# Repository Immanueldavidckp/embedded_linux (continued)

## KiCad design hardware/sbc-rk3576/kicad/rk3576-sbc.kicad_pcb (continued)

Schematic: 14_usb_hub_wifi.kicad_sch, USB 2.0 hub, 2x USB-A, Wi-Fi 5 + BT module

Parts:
C1401: 4.7uF; C_0402_1005Metric; MPN 0402 4.7uF 10V X5R
C1402, C1412: 100nF; C_0402_1005Metric; MPN 0402 100nF 10V X5R
C1403: 10uF; C_0603_1608Metric; MPN 0603 10uF 10V X5R
C1404, C1405, C1407, C1415: 100nF; C_0402_1005Metric; MPN 0402 100nF 6.3V X5R
C1406, C1408, C1414: 1uF; C_0402_1005Metric; MPN 0402 1uF 6.3V X5R
C1409, C1410: 22pF; C_0402_1005Metric; MPN 0402 22pF 50V C0G
C1411: 47uF; C_0805_2012Metric; MPN 0805 47uF 10V X5R
C1413: 22uF; C_0603_1608Metric; MPN 0603 22uF 10V X5R
C1416, C1417: DNP; C_0402_1005Metric; MPN 0402 DNP 6.3V X5R; not fitted
FB1401, FB1402: 120R@100MHz; L_0603_1608Metric; MPN BLM18PG121SN1D
J1401: USB2.0 A x2; USB_A_CUI_UJ2-ADH-TH_Horizontal_Stacked; MPN UJ2-ADH-TH
J1402: u.FL; U.FL_Hirose_U.FL-R-SMT-1_Vertical; MPN U.FL-R-SMT-1(10)
Q1401: BSS138; SOT-23; MPN BSS138; LCSC C52895
R1401: 2.7k; R_0402_1005Metric; MPN 0402 2.7k 1%
R1402, R1403, R1404, R1405, R1406: 10k; R_0402_1005Metric; MPN 0402 10k 1%
R1407: 100k; R_0402_1005Metric; MPN 0402 100k 1%
R1408: 0R; R_0402_1005Metric; MPN 0402 0R 1%
U1401: FE1.1s; SSOP-28_3.9x9.9mm_P0.635mm; MPN FE1.1S-BSOP28BCN; LCSC C9359
U1402, U1403: USBLC6-2SC6; SOT-23-6; MPN USBLC6-2SC6; LCSC C7519
U1404: AP2171W; SOT-23-5; MPN AP2171WG-7; LCSC C155555
U1405: BL-M8821CU1; WiFi_Module_22P_13.0x12.2mm_P1.27mm; MPN BL-M8821CU1 (alt BL-M8723DU1, JLC C9900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
Y1401: 12MHz; Crystal_SMD_3225-4Pin_3.2x2.5mm; MPN X322512MSB4SI (12MHz 20pF); LCSC C9002

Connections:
GND: C1401.2, C1402.2, C1403.2, C1404.2, C1405.2, C1406.2, C1407.2, C1408.2, C1409.2, C1410.2, C1411.2, C1412.2, C1413.2, C1414.2, C1415.2, C1416.2, C1417.2, J1401.4 (GND1), J1401.8 (GND2), J1401.9 (Shield), J1402.2 (Ext), Q1401.2 (S), R1401.2, R1407.2, U1401.1 (VSS), U1402.2 (GND), U1403.2 (GND), U1404.2 (GND), U1405.1 (GND), U1405.4 (GND), U1405.14 (GND), Y1401.2 (G), Y1401.4 (G); also elsewhere on the board
HUB_1V8: C1406.1, C1407.1, U1401.12 (VD18_O), U1401.28 (VD18)
HUB_3V3: C1403.1, C1404.1, C1405.1, R1402.2, R1403.2, U1401.13 (VD33), U1401.18 (VBUSM), U1401.19 (BUSJ), U1401.21 (VD33_O)
HUB_OVC_L: R1403.1, U1401.26 (OVCJ), U1404.3 (~FLG)
HUB_REXT: R1401.1, U1401.14 (REXT)
HUB_RST_L: C1408.1, R1402.1, U1401.17 (XRSTJ)
HUB_UP_DM: U1401.15 (DMU); also elsewhere on the board
HUB_UP_DP: U1401.16 (DPU); also elsewhere on the board
HUB_XI: C1409.1, U1401.3 (XIN), Y1401.1
HUB_XO: C1410.1, U1401.2 (XOUT), Y1401.3
USB3A_DM: U1401.10 (DM1); also elsewhere on the board
USB3A_DP: U1401.11 (DP1); also elsewhere on the board
USBA1_DM: J1401.2 (D1-), U1401.8 (DM2), U1402.3 (I/O2), U1402.4 (I/O2)
USBA1_DP: J1401.3 (D1+), U1401.9 (DP2), U1402.1 (I/O1), U1402.6 (I/O1)
USBA2_DM: J1401.6 (D2-), U1401.6 (DM3), U1403.3 (I/O2), U1403.4 (I/O2)
USBA2_DP: J1401.7 (D2+), U1401.7 (DP3), U1403.1 (I/O1), U1403.6 (I/O1)
USB_HOST_PWREN: U1404.4 (EN); also elsewhere on the board
VBUS_USB2A: C1411.1, C1412.1, J1401.1 (VBUS1), J1401.5 (VBUS2), U1402.5 (VBUS), U1403.5 (VBUS), U1404.1 (OUT)
VCC3V3_WIFI: C1413.1, C1414.1, C1415.1, FB1402.2, R1404.2, R1405.2, R1406.2, U1405.11 (VDD33)
VCC5V0_SYS_S5: FB1401.1, U1404.5 (IN); also elsewhere on the board
VCC5V_HUB: C1401.1, C1402.1, FB1401.2, U1401.20 (VDD5)
VCC_3V3_S3: FB1402.1; also elsewhere on the board
WIFI_ANT: C1417.1, J1402.1 (In), R1408.2
WIFI_BT_DIS_L: R1405.1, U1405.17 (~BT_DIS)
WIFI_CHIP_EN: Q1401.3 (D), R1406.1, U1405.18 (CHIP_EN)
WIFI_PD_GPIO: Q1401.1 (G), R1407.1; also elsewhere on the board
WIFI_RF: C1416.1, R1408.1, U1405.2 (RF)
WIFI_USB_DM: U1401.4 (DM4), U1405.12 (USB_DM)
WIFI_USB_DP: U1401.5 (DP4), U1405.13 (USB_DP)
WIFI_WL_DIS_L: R1404.1, U1405.16 (~WL_DIS)

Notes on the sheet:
14_usb_hub_wifi: USB 2.0 hub, 2x USB-A, Wi-Fi 5 + BT module

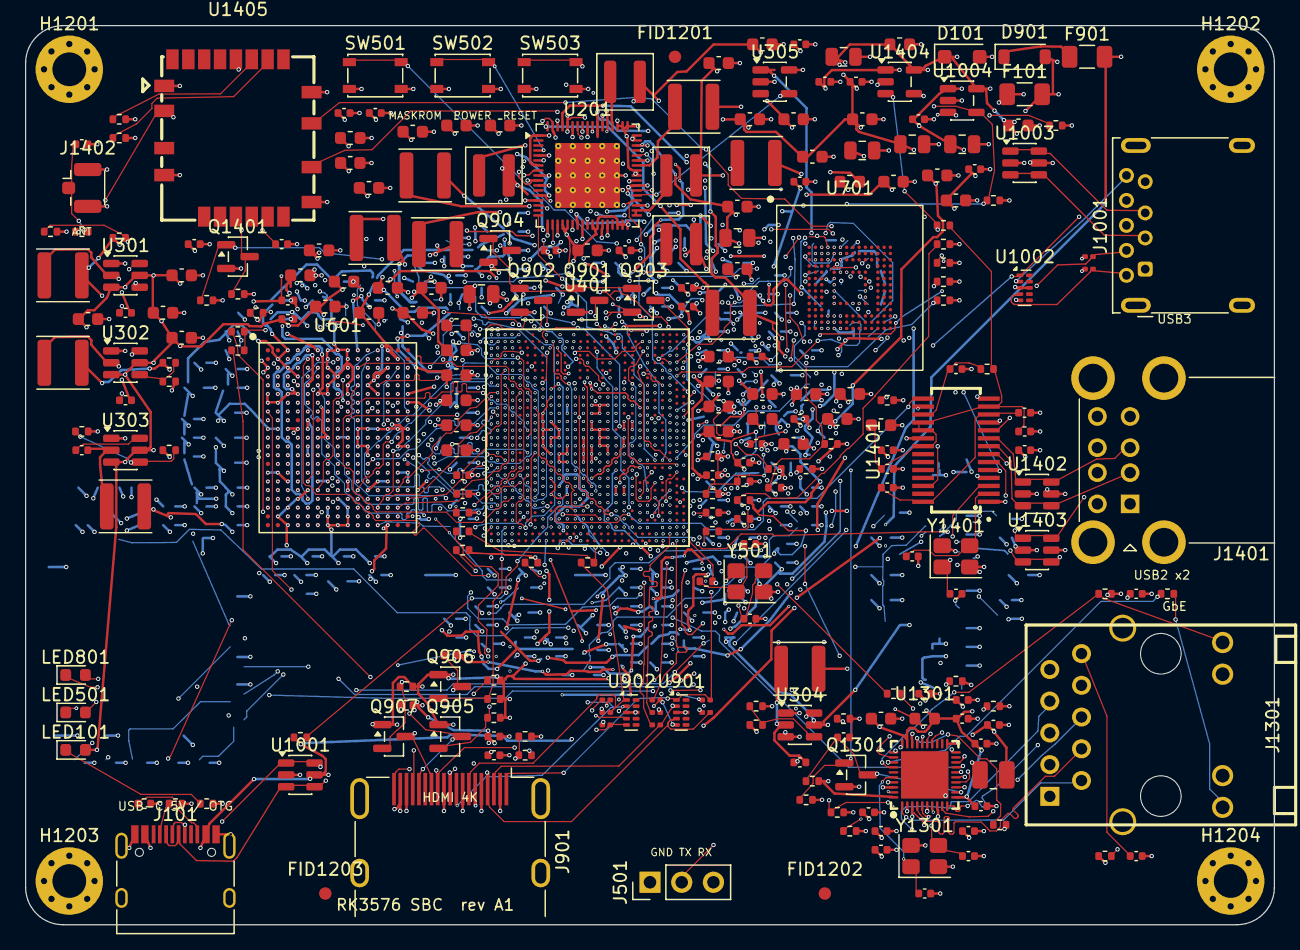
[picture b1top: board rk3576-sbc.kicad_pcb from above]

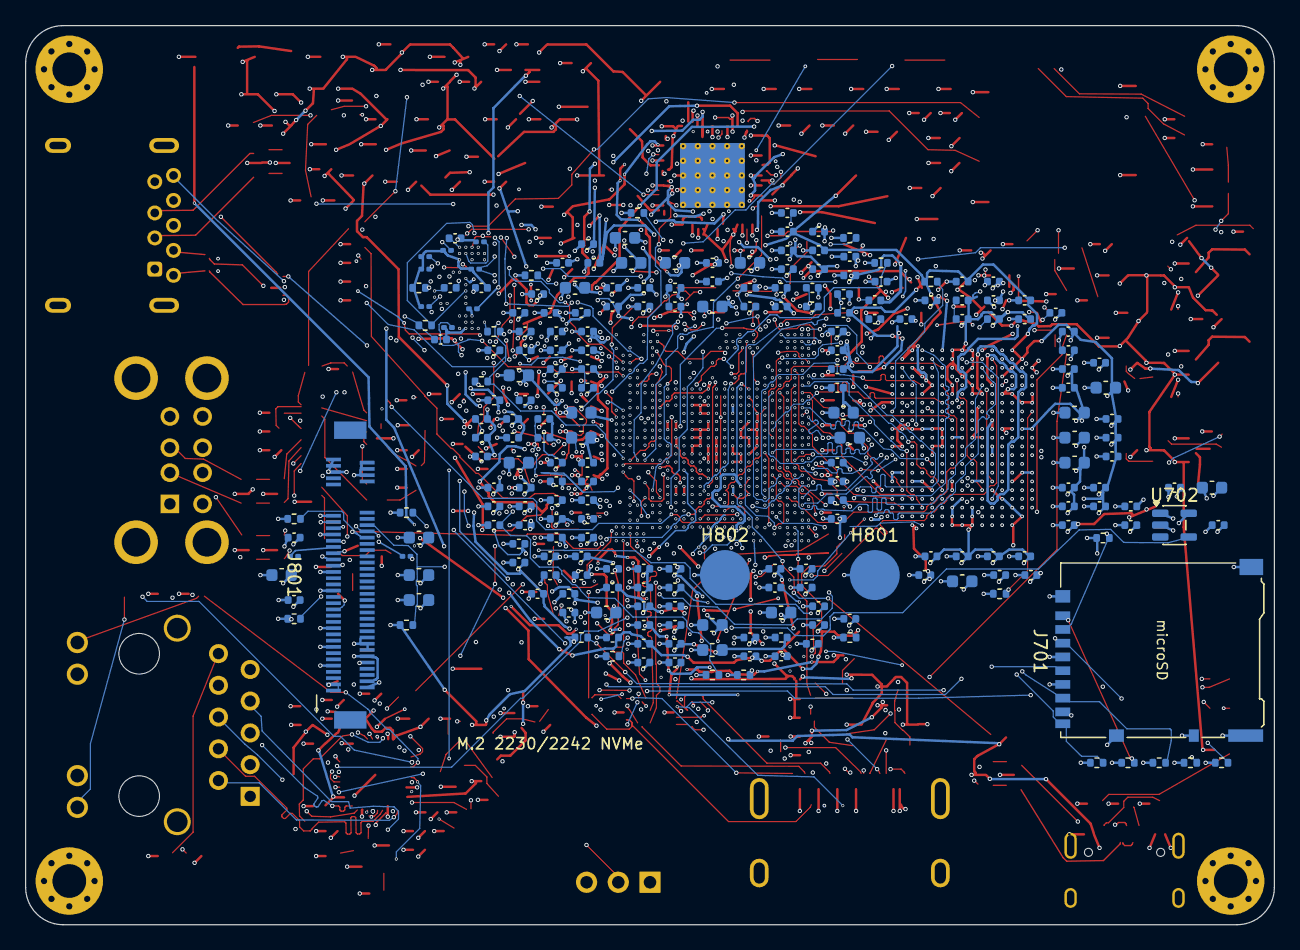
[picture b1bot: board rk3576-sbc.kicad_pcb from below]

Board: 10 copper layers, 100.0 x 72.0 mm, 484 parts (222 on the bottom side), 303 nets.

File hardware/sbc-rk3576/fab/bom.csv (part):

Qty,References,Value,Footprint,MPN,Manufacturer,LCSC,Unit USD,Ext USD,Populate,Notes
6,C101 C102 C205 C206 C1003 C1411,47uF,C_0805_2012Metric,0805 47uF 10V X5R,Samsung/Murata,,0.0300,0.180,,
33,C103 C104 C201 C207 C211 C215 C219 C222 C225 C228 C231 C234 C302 C306 C310 C314 C317 C403 C404 C418 C427 C436 C445 C446 C459 C467 C601 C602 C615 C621 C708 C1301 C1403,10uF,C_0603_1608Metric,0603 10uF 10V X5R,Samsung/Murata,,0.0040,0.132,,decoupling / various
5,C105 C910 C1004 C1402 C1412,100nF,C_0402_1005Metric,0402 100nF 10V X5R,Samsung/Murata,,0.0015,0.007,,
41,C202 C203 C204 C208 C209 C210 C212 C213 C214 C216 C217 C218 C220 C221 C223 C224 C226 C227 C229 C230 C232 C233 C235 C236 C303 C304 C307 C308 C311 C312 C315 C316 C401 C402 C417 C426 C435 C444 C803 C804 C1413,22uF,C_0603_1608Metric,0603 22uF 10V X5R,Samsung/Murata,,0.0120,0.492,,
12,C237 C238 C239 C240 C241 C242 C243 C244 C245 C246 C702 C705,2.2uF,C_0402_1005Metric,0402 2.2uF 6.3V X5R,Samsung/Murata,,0.0015,0.018,,decoupling / various
3,C247 C248 C249,4.7uF,C_0402_1005Metric,0402 4.7uF 6.3V X5R,Samsung/Murata,,0.0015,0.005,,decoupling / various
8,C250 C632 C1305 C1306 C1401 C4102 C4115 C4124,4.7uF,C_0402_1005Metric,0402 4.7uF 10V X5R,Samsung/Murata,,0.0015,0.012,,decoupling / various
40,C251 C318 C405 C406 C407 C408 C419 C420 C428 C429 C437 C438 C447 C448 C449 C460 C461 C468 C469 C478 C481 C486 C489 C492 C504 C603 C604 C616 C622 C623 C701 C1311 C1314 C1406 C1408 C1414 C4100 C4113 C4122 C4128,1uF,C_0402_1005Metric,0402 1uF 6.3V X5R,Samsung/Murata,,0.0015,0.060,,decoupling / various
2,C252 C909,1uF,C_0402_1005Metric,0402 1uF 10V X5R,Samsung/Murata,,0.0015,0.003,,decoupling / various
135,C301 C305 C309 C313 C409 C410 C411 C412 C413 C414 C415 C416 C421 C422 C423 C424 C425 C430 C431 C432 C433 C434 C439 C440 C441 C442 C443 C450 C451 C452 C453 C454 C455 C456 C457 C458 C462 C463 C464 C465 C466 C470 C471 C472 C473 C474 C475 C476 C477 C479 C480 C482 C483 C484 C485 C487 C488 C490 C491 C493 C494 C495 C496 C497 C498 C499 C503 C505 C605 C606 C607 C608 C609 C610 C611 C612 C613 C614 C617 C618 C619 C620 C624 C625 C626 C627 C628 C629 C630 C631 C633 C634 C703 C704 C706 C707 C709 C805 C806 C1302 C1303 C1304 C1307 C1308 C1309 C1310 C1315 C1316 C1404 C1405 C1407 C1415 C4101 C4103 C4104 C4105 C4106 C4107 C4108 C4109 C4110 C4111 C4112 C4114 C4116 C4117 C4118 C4119 C4120 C4121 C4123 C4125 C4126 C4127 C4129,100nF,C_0402_1005Metric,0402 100nF 6.3V X5R,Samsung/Murata,,0.0015,0.203,,decoupling / various
4,C501 C502 C1312 C1313,15pF,C_0402_1005Metric,0402 15pF 50V C0G,Samsung/Murata,,0.0015,0.006,,
10,C801 C802 C901 C902 C903 C904 C905 C906 C907 C908,220nF,C_0201_0603Metric,0201 220nF 6.3V X5R,Samsung/Murata,,0.0010,0.010,,decoupling / various
2,C1001 C1002,100nF,C_0201_0603Metric,0201 100nF 6.3V X5R,Samsung/Murata,,0.0010,0.002,,SS TX AC cap
2,C1409 C1410,22pF,C_0402_1005Metric,0402 22pF 50V C0G,Samsung/Murata,,0.0015,0.003,,
1,D101,SMF5.0A,D_SOD-123F,SMF5.0A,Littelfuse/MDD,C123799,0.0300,0.030,,5V TVS on VBUS
1,D901,B5819W,D_SOD-123,B5819W,CJ,C8598,0.0100,0.010,,
1,F101,6A,Fuse_1206_3216Metric,1206L600/8SLY (6A fast),Littelfuse/BHFUSE,,0.0600,0.060,,Input fuse
1,F901,0.5A PTC,Fuse_1206_3216Metric,1206L050/15YR,Littelfuse/BHFUSE,,0.0300,0.030,,
4,FB301 FB1301 FB1401 FB1402,120R@100MHz,L_0603_1608Metric,BLM18PG121SN1D,Murata,,0.0200,0.080,,
1,H801,M2 standoff 2242,SMD_Standoff_M2_D4.0mm,9774020243R (M2 SMD standoff),Wurth,,0.1500,0.150,,M.2 2242 card retention
1,H802,M2 standoff 2230,SMD_Standoff_M2_D4.0mm,9774020243R (M2 SMD standoff),Wurth,,0.1500,0.150,,M.2 2230 card retention
1,J101,USB-C PWR/OTG,USB_C_Receptacle_HRO_TYPE-C-31-M-12,TYPE-C-31-M-12,Korean Hroparts,C165948,0.1000,0.100,,"USB-C 16P receptacle, power in + USB2 OTG0"
1,J501,DEBUG UART,PinHeader_1x03_P2.54mm_Vertical,2.54mm 1x3 pin header,generic,,0.0200,0.020,,1:GND 2:TX(out) 3:RX(in)
1,J701,microSD,microSD_HC_Hirose_DM3AT-SF-PEJM5,DM3AT-SF-PEJM5,Hirose,,0.6000,0.600,,microSD push-push with detect
1,J801,M.2 M-KEY,M.2_Socket3_M-Key_H4.2mm,"APCI0026-P001A (M.2 M key, H4.2)",LOTES,,0.4000,0.400,,"M.2 2230/2242 NVMe, PCIe2.1 x1 (lane 0 only)"
1,J901,HDMI,HDMI_A_Molex_208658-1001_Horizontal,208658-1001,Molex,,0.4500,0.450,,"HDMI type A, 4K@60 (TMDS) / 4K@120 (FRL)"
1,J1001,USB3.0 A,USB3_A_Molex_48393-001,48393-0001,Molex,,0.4500,0.450,,USB 3.0 type-A host (5Gbps)
1,J1301,RJ45 GbE,RJ45_Hanrun_HR911130C_MagJack,HR911130C,HanRun,C50933,0.5500,0.550,,RJ45 + 1000BASE-T magnetics + LEDs
1,J1401,USB2.0 A x2,USB_A_CUI_UJ2-ADH-TH_Horizontal_Stacked,UJ2-ADH-TH,CUI,,0.5500,0.550,,dual stacked USB 2.0 A (keyboard + mouse)
1,J1402,u.FL,U.FL_Hirose_U.FL-R-SMT-1_Vertical,U.FL-R-SMT-1(10),Hirose,,0.2500,0.250,,"Wi-Fi/BT antenna (2.4/5 GHz dipole, IPEX cable)"
1,L201,0.24uH,L_Coilcraft_XAL4030-XXX,MDA4030-R24M (0.24uH 8A),Sunlord/Changjiang,,0.1200,0.120,,BUCK1 VDD_CPU_BIG_S0 0.55-0.95V
3,L202 L203 L204,0.47uH,L_Coilcraft_XAL4030-XXX,MDA4030-R47M (0.47uH 5.5A),Sunlord/Changjiang,,0.1000,0.300,,decoupling / various
6,L205 L206 L207 L208 L209 L210,1uH,L_Changjiang_FNR4030S,FNR4030S1R0NT (1uH 3.4A),Sunlord/Changjiang,,0.0500,0.300,,decoupling / various
3,L301 L302 L303,2.2uH,L_Changjiang_FNR4030S,FNR4030S2R2MT,Changjiang,,0.0500,0.150,,
1,L304,1.5uH,L_Changjiang_FNR4030S,FNR4030S1R5MT,Changjiang,,0.0500,0.050,,
1,L1301,2.2uH,L_1008_2520Metric,MWSA2520S-2R2MT (2.2uH 1.5A),Sunlord,,0.0300,0.030,,RTL8211F switching regulator inductor
1,LED101,PWR,LED_0603_1608Metric,19-217/GHC-YR1S2/3T,Everlight,C72043,0.0100,0.010,,Green power LED
1,LED501,SYS,LED_0603_1608Metric,19-217/BHC-ZL1M2RY/3T,Everlight,C72041,0.0100,0.010,,Blue status LED
1,LED801,SSD,LED_0603_1608Metric,19-217/GHC-YR1S2/3T,Everlight,C72043,0.0100,0.010,,SSD activity
9,Q901 Q902 Q903 Q904 Q905 Q906 Q907 Q1301 Q1401,BSS138,SOT-23,BSS138,onsemi/CJ,C52895,0.0100,0.090,,decoupling / various
2,R101 R102,5.1k,R_0402_1005Metric,0402 5.1k 1%,Yageo/UniOhm,,0.0005,0.001,,Rd: advertise sink
3,R103 R211 R212,2.2k,R_0402_1005Metric,0402 2.2k 1%,Yageo/UniOhm,,0.0005,0.002,,
6,R201 R203 R205 R207 R209 R1408,0R,R_0402_1005Metric,0402 0R 1%,Yageo/UniOhm,,0.0005,0.003,,decoupling / various
26,R213 R214 R302 R304 R306 R308 R502 R602 R701 R710 R711 R712 R713 R714 R715 R801 R802 R803 R915 R1003 R1305 R1402 R1403 R1404 R1405 R1406,10k,R_0402_1005Metric,0402 10k 1%,Yageo/UniOhm,,0.0005,0.013,,decoupling / various
1,R301,16k,R_0402_1005Metric,0402 16k 1%,Yageo/UniOhm,,0.0005,0.001,,
1,R303,4.3k,R_0402_1005Metric,0402 4.3k 1%,Yageo/UniOhm,,0.0005,0.001,,
1,R305,1.74k,R_0402_1005Metric,0402 1.74k 1%,Yageo/UniOhm,,0.0005,0.001,,
1,R307,33k,R_0402_1005Metric,0402 33k 1%,Yageo/UniOhm,,0.0005,0.001,,
1,R503,100R,R_0402_1005Metric,0402 100R 1%,Yageo/UniOhm,,0.0005,0.001,,
2,R504 R804,1k,R_0402_1005Metric,0402 1k 1%,Yageo/UniOhm,,0.0005,0.001,,
3,R505 R506 R601,240R,R_0402_1005Metric,0402 240R 1%,Yageo/UniOhm,,0.0005,0.002,,decoupling / various
8,R702 R703 R704 R705 R706 R707 R708 R709,10k,R_0201_0603Metric,0201 10k 1%,Yageo/UniOhm,,0.0006,0.005,,
6,R716 R917 R1002 R1004 R1306 R1407,100k,R_0402_1005Metric,0402 100k 1%,Yageo/UniOhm,,0.0005,0.003,,decoupling / various
8,R901 R902 R903 R904 R905 R906 R907 R908,590R,R_0402_1005Metric,0402 590R 1%,Yageo/UniOhm,,0.0005,0.004,,
7,R909 R911 R913 R1307 R1308 R1309 R1310,4.7k,R_0402_1005Metric,0402 4.7k 1%,Yageo/UniOhm,,0.0005,0.004,,decoupling / various
2,R910 R912,1.8k,R_0402_1005Metric,0402 1.8k 1%,Yageo/UniOhm,,0.0005,0.001,,
1,R914,27k,R_0402_1005Metric,0402 27k 1%,Yageo/UniOhm,,0.0005,0.001,,
1,R916,20k,R_0402_1005Metric,0402 20k 1%,Yageo/UniOhm,,0.0005,0.001,,
1,R1001,56k,R_0402_1005Metric,0402 56k 1%,Yageo/UniOhm,,0.0005,0.001,,VBUS detect divider (5V -> 3.2V)
2,R1301 R1302,22R,R_0402_1005Metric,0402 22R 1%,Yageo/UniOhm,,0.0005,0.001,,decoupling / various
1,R1303,2.49k,R_0402_1005Metric,0402 2.49k 1%,Yageo/UniOhm,,0.0005,0.001,,RSET 1%
1,R1304,1.5k,R_0402_1005Metric,0402 1.5k 1%,Yageo/UniOhm,,0.0005,0.001,,MDIO pull-up
2,R1311 R1312,510R,R_0402_1005Metric,0402 510R 1%,Yageo/UniOhm,,0.0005,0.001,,
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
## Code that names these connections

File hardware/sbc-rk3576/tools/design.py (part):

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          {'1': 'GND', '2': 'DBG_UART_TX', '3': 'DBG_UART_RX'},
          mpn='2.54mm 1x3 pin header', mfr='generic', price=0.02, desc='1:GND 2:TX(out) 3:RX(in)')
    # Status LED (sinks into GPIO, 3.3V bank)
    S('GPIO0_C5', 'LED_SYS_L')
    d.add('LED', 'Device:LED', 'SYS', 'LED_SMD:LED_0603_1608Metric', {'1': 'LED_SYS_L', '2': 'LED_SYS_A'},
          mpn='19-217/BHC-ZL1M2RY/3T', mfr='Everlight', lcsc='C72041', price=0.01, desc='Blue status LED')
    d.R('1k', 'LED_SYS_A', 'VCC_3V3_S0')
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    S('PCIE0_RXN', 'PCIE0_RXN')
    S('PCIE0_REFCLKP', 'PCIE0_REFCLKP')
    S('PCIE0_REFCLKN', 'PCIE0_REFCLKN')
    S('GPIO4_C7', 'PCIE0_PERST_L')
    S('PCIE0_CLKREQN_M3', 'PCIE0_CLKREQ_L')
    S('GPIO4_C4', 'PCIE0_WAKE_L')
    d.R('10k', 'PCIE0_CLKREQ_L', 'VCC_3V3_S0')
    d.R('10k', 'PCIE0_WAKE_L', 'VCC_3V3_S0')
    d.R('10k', 'PCIE0_PERST_L', 'GND', desc='hold SSD in reset until driver releases')
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              {'1': f'HDMI_{a}P_C', '2': f'HDMI_{a}N_C', '3': 'GND', '4': f'HDMI_{b}P_C',
               '5': f'HDMI_{b}N_C', '8': 'GND', '6': None, '7': None, '9': None, '10': None},
              mpn='TPD4E05U06DQAR', mfr='Texas Instruments', price=0.18, desc='TMDS ESD 0.5pF')
    S('GPIO4_D1', 'HDMI_TX_ON_H')
    # DDC / CEC: BSS138 bidirectional level shifters (3.3V <-> 5V)
    for sig, func in [('SCL', 'HDMI_TX_SCL'), ('SDA', 'HDMI_TX_SDA'), ('CEC', 'HDMI_TX_CEC_M0')]:
        lo = f'HDMI_{sig}'
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          {'1': 'VBUS_USB3A', '2': 'GND', '3': 'USB3A_OC_L', '4': 'USB_HOST_PWREN', '5': 'VCC5V0_SYS_S5'},
          mpn='AP2171WG-7 (1.5A limit)', mfr='Diodes Inc', lcsc='C155555', price=0.12,
          desc='USB-A VBUS switch, 900mA USB3 budget')
    S('GPIO0_C4', 'USB_HOST_PWREN')
    S('GPIO0_C6', 'USB3A_OC_L')
    d.R('10k', 'USB3A_OC_L', 'VCC_3V3_S3')
    d.R('100k', 'USB_HOST_PWREN', 'GND')
    d.caps('VBUS_USB3A', '1x47uF/0805 1x100nF')
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    # reset: RC power-on reset + open-drain override from a GPIO (level independent)
    d.R('10k', 'PHY_RST_L', 'VCC3V3_PHY')
    d.C('1uF', 'PHY_RST_L')
    S('GPIO1_D0', 'PHY_RST_GPIO')
    d.add('Q', 'Transistor_FET:BSS138', 'BSS138', 'Package_TO_SOT_SMD:SOT-23',
          {'1': 'PHY_RST_GPIO', '2': 'GND', '3': 'PHY_RST_L'},
          mpn='BSS138', mfr='onsemi/CJ', lcsc='C52895', price=0.01, desc='PHY reset (GPIO high = reset)')
    d.R('100k', 'PHY_RST_GPIO', 'GND')
    S('GPIO1_D1', 'PHY_INT_L')
    d.R('4.7k', 'PHY_INT_L', 'VCC_1V8_S3', desc='INTB open-drain pull-up')
    # Straps: CFG_LDO[1:0] (LED2,LED1) select RGMII IO level; 1.8 V = LED2 high, LED1 low
    # (verify against RTL8211F datasheet strap table). CFG_EXT (LED0) low.
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    d.R('10k', 'WIFI_WL_DIS_L', 'VCC3V3_WIFI')
    d.R('10k', 'WIFI_BT_DIS_L', 'VCC3V3_WIFI')
    d.R('10k', 'WIFI_CHIP_EN', 'VCC3V3_WIFI')
    S('GPIO1_D2', 'WIFI_PD_GPIO')
    d.add('Q', 'Transistor_FET:BSS138', 'BSS138', 'Package_TO_SOT_SMD:SOT-23',
          {'1': 'WIFI_PD_GPIO', '2': 'GND', '3': 'WIFI_CHIP_EN'},
          mpn='BSS138', mfr='onsemi/CJ', lcsc='C52895', price=0.01, desc='Wi-Fi power-down (GPIO high = off)')
    d.R('100k', 'WIFI_PD_GPIO', 'GND')
    # antenna: 50R CPWG to a u.FL, pi-match footprints (series 0R, shunts DNP)
    d.R('0R', 'WIFI_RF', 'WIFI_ANT', size='0402', desc='RF pi-match series')
    d.C('DNP', 'WIFI_RF', size='0402', dnp=True, desc='RF pi-match shunt')
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
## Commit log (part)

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2026-06-01 Tailor CLAUDE.md to Radxa A5E / Pico / EC200U hardware
2026-06-04 day2: ring buffer rewritten from memory (david)
2026-06-04 restructure: topic-wise layout (advanced-c/<topic>)
2026-06-04 architecture update
2026-06-07 plans update
